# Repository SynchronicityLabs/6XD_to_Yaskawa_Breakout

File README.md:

# 6XD_to_Yaskawa_Breakout

This is a PCB breakout board designed for connecting Yaskawa servo drives to Duet3D control boards.  Specifically, it was developed to simplify connection between a Duet 3 6XD board and a pair of Yaskawa Sigma-7 SGD7S-****00A series servo drives—i.e., step/dir-capable drives.  These drives range from 50W to 15kW, with the 50W to 400W versions (10-400W motors) being available in 100VAC or 200VAC single-phase.

This should be considered in beta! It is working on my drives, but use at your own risk!

## The board serves the following functions:
-	Correct voltage mismatch in Step/Direction signal.  The 6XD drives these signals at 5V, the SGD7S wants 3.3V
-	Allow enabling “Servo On” from the 6XD’s Dx_EN(-) pin.  The SGD7S uses a 24V enable signal which the 6XD enable pins cannot drive directly.  Set 6XD's enable jumper to "active disable".
-	Combines the torque-limit enable for forward and reverse (these are 2 separate inputs) and from both drives, to allow a single optoisolated output to trigger torque limiting for both drives, in both directions (e.g., during homing or moves prior to homing).
-	Combine the alarm reset signal for both drives to use a single optoisolated output
-	Combine the P-control enable signal for both drives to use a single optoisolated output
-	Provide a jumper to select two outputs between P-Control and two open terminal block connections (i.e., you can connect 2 of the 3)
- Block terminals and jumper allow reconfiguration of various inputs/outputs from default if desired.

### Do I need this to connect to a SGD7S servo drive?
No.  None of the connections made on the board are particularly bulky or complex; the necessary components could be joined directly into the wiring between the 6XD and SGD7S’s CN1 connector if preferred.

### Could I use this to connect a 1XD or other Duet board to a SGD7S drive?
Not recommended.  Other boards could be used, but not with the circuitry on this breakout board.  While it may seem that the 1XD would be a simple stand-in for the 6XD, it cannot directly handle the step/dir signal current for the SGD7S and would need line-driver type setup. Additionally, it cannot directly interface with the necessary inputs via IO pins (though OUT_0 and OUT_1 could), as the 6XD’s optoisolated outputs can.

### What if I want to connect more than two drives?
You could use multiple breakout boards (up to three) on a 6XD.  The opto-isolated outputs could be daisy-chained, however, you may need to ration them carefully.  The 6XD has four, with current limits of 50mA.  Each alarm-reset, P-Control, and torque-limit input takes 5mA.  So, six drives is not a problem for parallel outputs in most cases, however torque-limit signals from a single output would be maxed out at 5 drives. 

### Where do I find you if I blow up my drives/Duet?
You don’t, this is currently beta-version at best.  The SGD7S manual is nearly 650 pages.  I’ve tried to make it simple here, but it isn’t.  Your drive connections are at your own risk.

### Can it interface to drives other than the SGD7S drives?
Probably.  Good luck, we all believe in you.

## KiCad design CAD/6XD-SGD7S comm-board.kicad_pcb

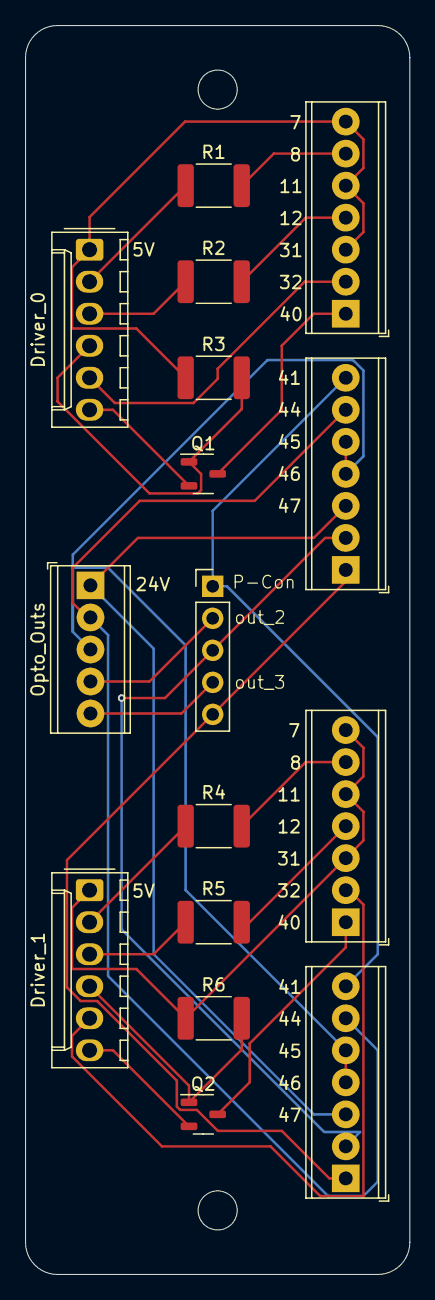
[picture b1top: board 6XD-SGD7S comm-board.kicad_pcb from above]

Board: 2 copper layers, 30.5 x 99.1 mm, 16 parts (0 on the bottom side), 26 nets.

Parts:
J1: Driver_0; Molex_KK-254_AE-6410-06A_1x06_P2.54mm_Vertical
J2: Opto_Outs; TerminalBlock_Phoenix_MPT-0,5-5-2.54_1x05_P2.54mm_Horizontal
J3: Driver_1; Molex_KK-254_AE-6410-06A_1x06_P2.54mm_Vertical
J5, J7: Conn_01x07_Socket; TerminalBlock_Phoenix_MPT-0,5-7-2.54_1x07_P2.54mm_Horizontal
J6: Out_Select; PinHeader_1x05_P2.54mm_Vertical
J8: Driver_0_Out; TerminalBlock_Phoenix_MPT-0,5-7-2.54_1x07_P2.54mm_Horizontal
J9: Driver_1_Out; TerminalBlock_Phoenix_MPT-0,5-7-2.54_1x07_P2.54mm_Horizontal
Q1, Q2: 2N7002NXAKR; SOT-23-3
R1, R2, R4, R5: 100R; R_1812_4532Metric_Pad1.30x3.40mm_HandSolder
R3, R6: 10kR; R_1812_4532Metric_Pad1.30x3.40mm_HandSolder

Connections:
/5V: J1.1, J8.3, J8.5, J8.7, R3.1
/5V_2: J3.1, J9.3, J9.5, J9.7, R6.1
/Dir(-): J1.3, R2.1
/Dir(-)_2: J3.3, R5.1
/En(-): J1.4, Q1.1 (G), R3.2
/En(-)_2: J3.4, Q2.1 (G), R6.2
/Err: J1.5, J8.2
/Err_2: J3.5, J9.2
/GND: J1.6, Q1.2 (S)
/GND_2: J3.6, Q2.2 (S)
/IO0_out_iso_pos: J2.2, J5.6, J7.6
/IO1_out_iso_pos: J2.3, J5.4, J5.5, J7.4, J7.5
/IO2_out_iso_pos: J2.4, J6.2
/IO3_out_iso_pos: J2.5, J6.4
/Step(-): J1.2, R1.1
/Step(-)_2: J3.2, R4.1
/VFuseIO: J2.1, J5.3, J7.3
unnamed: J5.1, J6.5, J7.1
unnamed: J5.2, J6.3, J7.2
unnamed: J5.7, J6.1, J7.7
unnamed: J8.1, Q1.3 (D)
unnamed: J8.4, R2.2
unnamed: J8.6, R1.2
unnamed: J9.1, Q2.3 (D)
unnamed: J9.4, R5.2
unnamed: J9.6, R4.2
